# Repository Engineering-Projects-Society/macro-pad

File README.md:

View this project on [CADLAB.io](https://cadlab.io/project/26023). 

# macro-pad

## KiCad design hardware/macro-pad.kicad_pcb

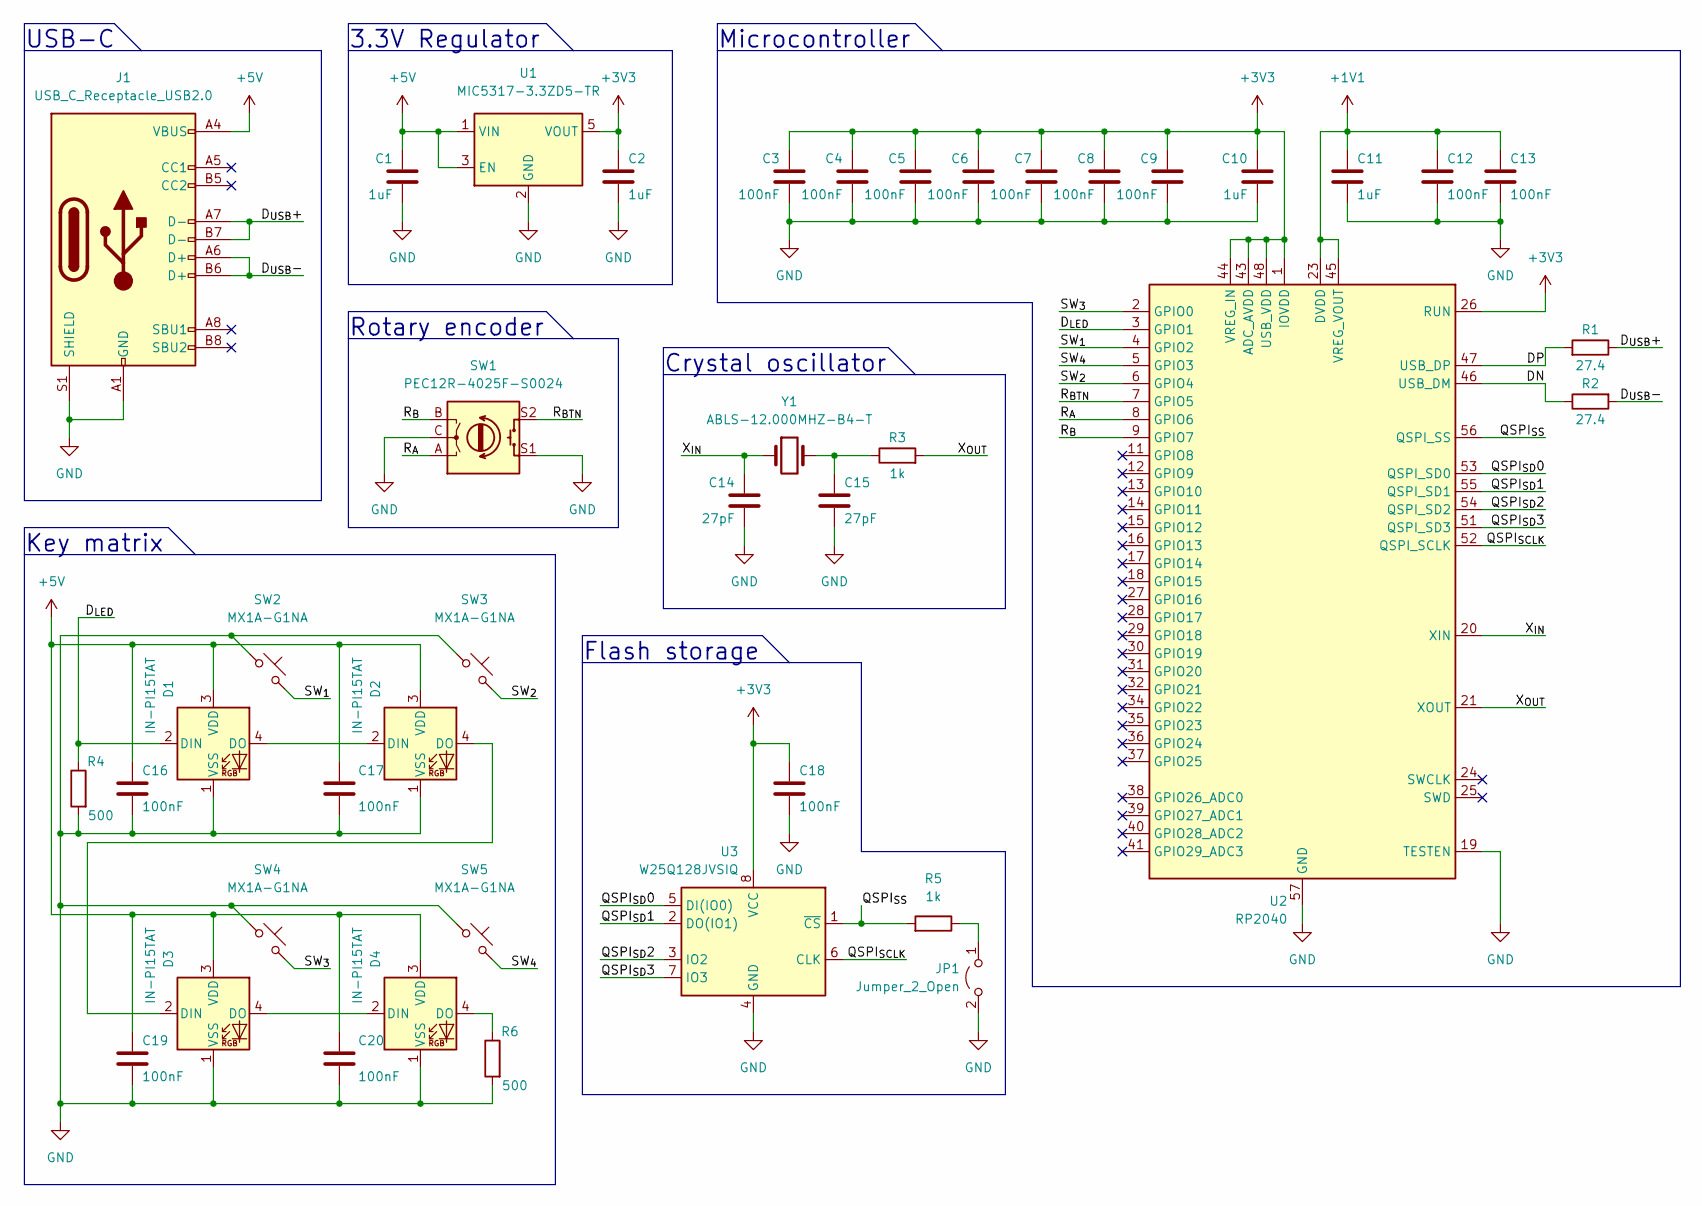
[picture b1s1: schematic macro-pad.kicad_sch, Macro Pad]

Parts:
C1, C2, C10, C11: 1uF; C_0402_1005Metric
C3, C4, C5, C6, C7, C8, C9, C12, C13, C16, C17, C18, C19, C20: 100nF; C_0402_1005Metric
C14, C15: 27pF; C_0402_1005Metric
D1, D2, D3, D4: IN-PI15TAT; LED_SK6812_EC15_1.5x1.5mm
J1: USB_C_Receptacle_USB2.0; USB_C_Receptacle_XKB_U262-16XN-4BVC11
JP1: Jumper_2_Open; PinHeader_1x02_P2.54mm_Vertical
R1, R2: 27.4; R_0402_1005Metric
R3, R5: 1k; R_0402_1005Metric
R4, R6: 500; R_0402_1005Metric
SW1: PEC12R-4025F-S0024; RotaryEncoder_Alps_EC11E-Switch_Vertical_H20mm
SW2, SW3, SW4, SW5: MX1A-G1NA; SW_Cherry_MX_1.00u_PCB
U1: MIC5317-3.3ZD5-TR; SOT-23-5
U2: RP2040; QFN-56-1EP_7x7mm_P0.4mm_EP3.2x3.2mm
U3: W25Q128JVSIQ; SOIC-8_5.23x5.23mm_P1.27mm
Y1: ABLS-12.000MHZ-B4-T; Crystal_SMD_HC49-SD

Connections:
+1V1: C11.1, C12.1, C13.1, U2.23 (DVDD), U2.45 (VREG_VOUT), U2.50 (DVDD)
+3V3: C2.1, C3.1, C4.1, C5.1, C6.1, C7.1, C8.1, C9.1, C10.1, C18.1, U1.5 (VOUT), U2.1 (IOVDD), U2.10 (IOVDD), U2.22 (IOVDD), U2.26 (RUN), U2.33 (IOVDD), U2.42 (IOVDD), U2.43 (ADC_AVDD), U2.44 (VREG_IN), U2.48 (USB_VDD), U2.49 (IOVDD), U3.8 (VCC)
+5V: C1.1, C16.1, C17.1, C19.1, C20.1, D1.3 (VDD), D2.3 (VDD), D3.3 (VDD), D4.3 (VDD), J1.A4 (VBUS), J1.A9 (VBUS), J1.B4 (VBUS), J1.B9 (VBUS), U1.1 (VIN), U1.3 (EN)
/DN: R2.1, U2.46 (USB_DM)
/DP: R1.2, U2.47 (USB_DP)
/D_{LED}: D1.2 (DIN), R4.1, U2.3 (GPIO1)
/D_{USB}+: J1.A7 (D-), J1.B7 (D-), R1.1
/D_{USB}-: J1.A6 (D+), J1.B6 (D+), R2.2
/QSPI_{SCLK}: U2.52 (QSPI_SCLK), U3.6 (CLK)
/QSPI_{SD}0: U2.53 (QSPI_SD0), U3.5 (DI(IO0))
/QSPI_{SD}1: U2.55 (QSPI_SD1), U3.2 (DO(IO1))
/QSPI_{SD}2: U2.54 (QSPI_SD2), U3.3 (IO2)
/QSPI_{SD}3: U2.51 (QSPI_SD3), U3.7 (IO3)
/QSPI_{SS}: R5.2, U2.56 (QSPI_SS), U3.1 (~CS)
/R_{A}: SW1.A, U2.8 (GPIO6)
/R_{BTN}: SW1.S2, U2.7 (GPIO5)
/R_{B}: SW1.B, U2.9 (GPIO7)
/SW_{1}: SW2.2, U2.4 (GPIO2)
/SW_{2}: SW3.2, U2.6 (GPIO4)
/SW_{3}: SW4.2, U2.2 (GPIO0)
/SW_{4}: SW5.2, U2.5 (GPIO3)
/X_{IN}: C14.1, U2.20 (XIN), Y1.1
/X_{OUT}: R3.2, U2.21 (XOUT)
GND: C1.2, C2.2, C3.2, C4.2, C5.2, C6.2, C7.2, C8.2, C9.2, C10.2, C11.2, C12.2, C13.2, C14.2, C15.2, C16.2, C17.2, C18.2, C19.2, C20.2, D1.1 (VSS), D2.1 (VSS), D3.1 (VSS), D4.1 (VSS), J1.A1 (GND), J1.A12 (GND), J1.B1 (GND), J1.B12 (GND), J1.S1 (SHIELD), JP1.2 (B), R4.2, R6.2, SW1.C, SW1.S1, SW2.1, SW3.1, SW4.1, SW5.1, U1.2 (GND), U2.19 (TESTEN), U2.57 (GND), U3.4 (GND)
unnamed: C15.1, R3.1, Y1.2
unnamed: D1.4 (DO), D2.2 (DIN)
unnamed: D2.4 (DO), D3.2 (DIN)
unnamed: D3.4 (DO), D4.2 (DIN)
unnamed: D4.4 (DO), R6.1
unnamed: JP1.1 (A), R5.1

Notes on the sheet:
USB-C
Flash storage
Microcontroller
Crystal oscillator
3.3V Regulator
Key matrix
Rotary encoder

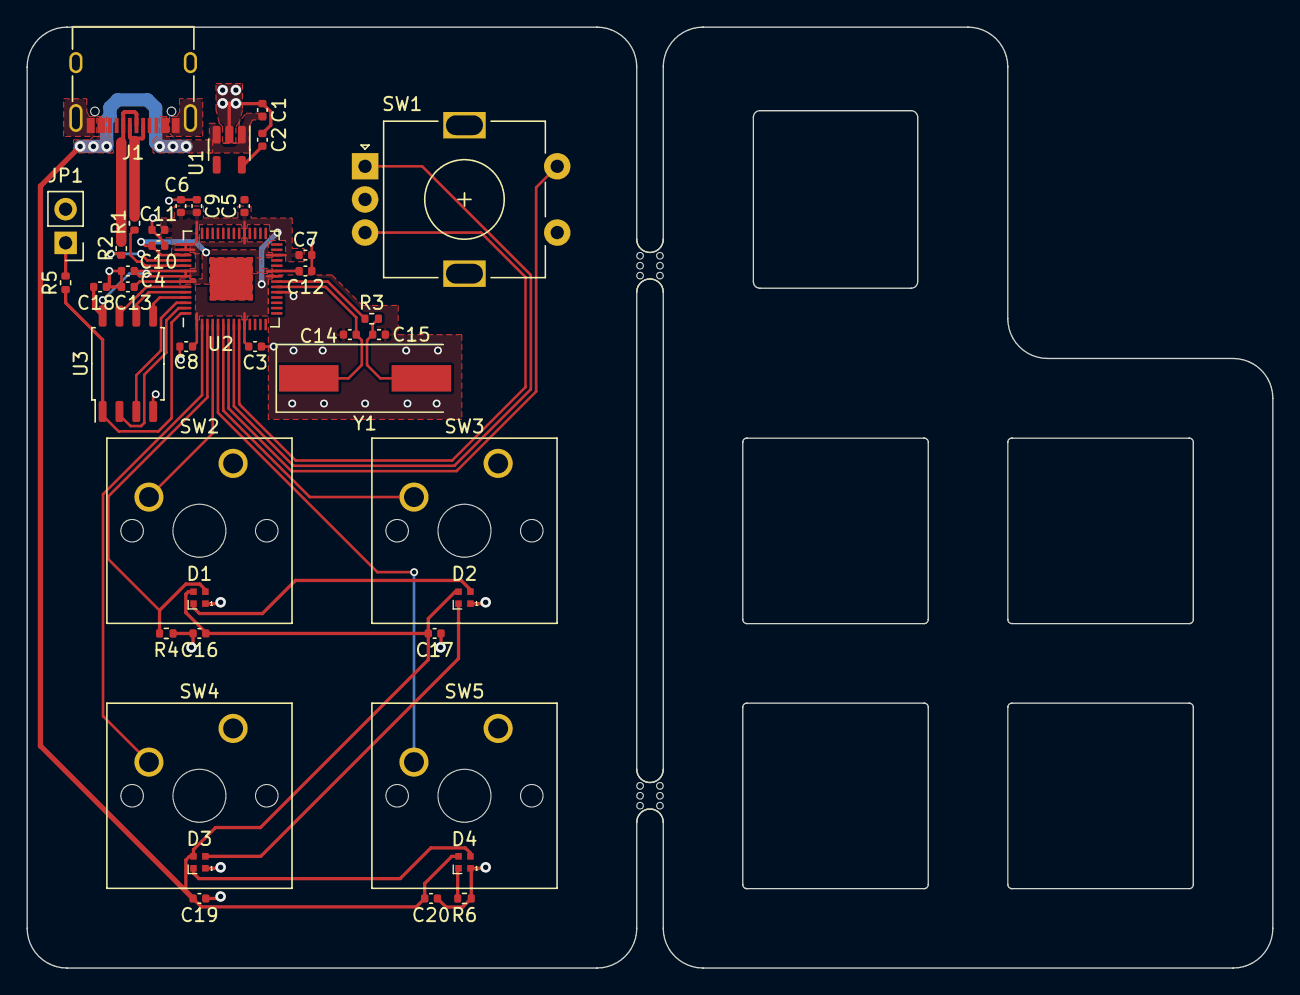
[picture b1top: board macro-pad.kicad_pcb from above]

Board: 2 copper layers, 94.0 x 71.0 mm, 43 parts (0 on the bottom side), 30 nets.

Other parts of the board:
mouse-bite-2mm-slot, mouse-bite-2mm-slot#2: VAL**; mouse-bite-2mm-slot

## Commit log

2022-10-03 Added basic escema circuit
2022-10-03 Backlink to CADLAB.io has been added.
2022-10-03 Linear-reg was subsituted with a MIC5317
2022-10-03 Added RP2040 symbol and footprint
2022-10-03 Removed legacy SC09087 symbol and footprint
2022-10-03 Revert changes @ddaff18282d14ea0292484e835075d08a0579ae8
2022-10-03 Added microcontroller symbol, power and USB data
2022-10-03 Added quarz crystal and wired up flash memory
2022-10-03 Added rotary encoder circuit
2022-10-03 Box drawing, labelling and rearranging of components
2022-10-03 Added schematic description
2022-10-03 Components have been annotated
2022-10-03 All symbols have been associated with a footprint
2022-10-03 Replaced capacitor footprints with bigger ones
2022-10-04 Added panelization footprints
2022-10-04 Added basic board layout
2022-10-04 Resized PCB and added some comonents
2022-10-04 Completed power section
2022-10-04 Wired swicthes to be pulled down if actived instead of up
2022-10-04 Corrected SMD LED footprint
2022-10-04 Set resistors and capacitors to use a smaller footprint and chnaged to non-handsolder
2022-10-04 Reversed RGB LED data path for easier routing
2022-10-04 Added LED data and power traces
2022-10-04 Fixed invlid 3.3V flag
2022-10-04 Added lables to USB section for easier routing
2022-10-04 Processor and memory secion finished and wired up
2022-10-04 Added switch 3D model
2022-10-04 Rearranged silkscreen letters for readability
2022-10-04 Rearranged micocontroller pins for easier routing
2022-10-04 PCB components have been routed
2022-10-04 Added some decorative patterns
